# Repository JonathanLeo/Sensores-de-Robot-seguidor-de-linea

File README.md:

# Sensores-de-Robot-seguidor-de-linea
Esquemático y Board

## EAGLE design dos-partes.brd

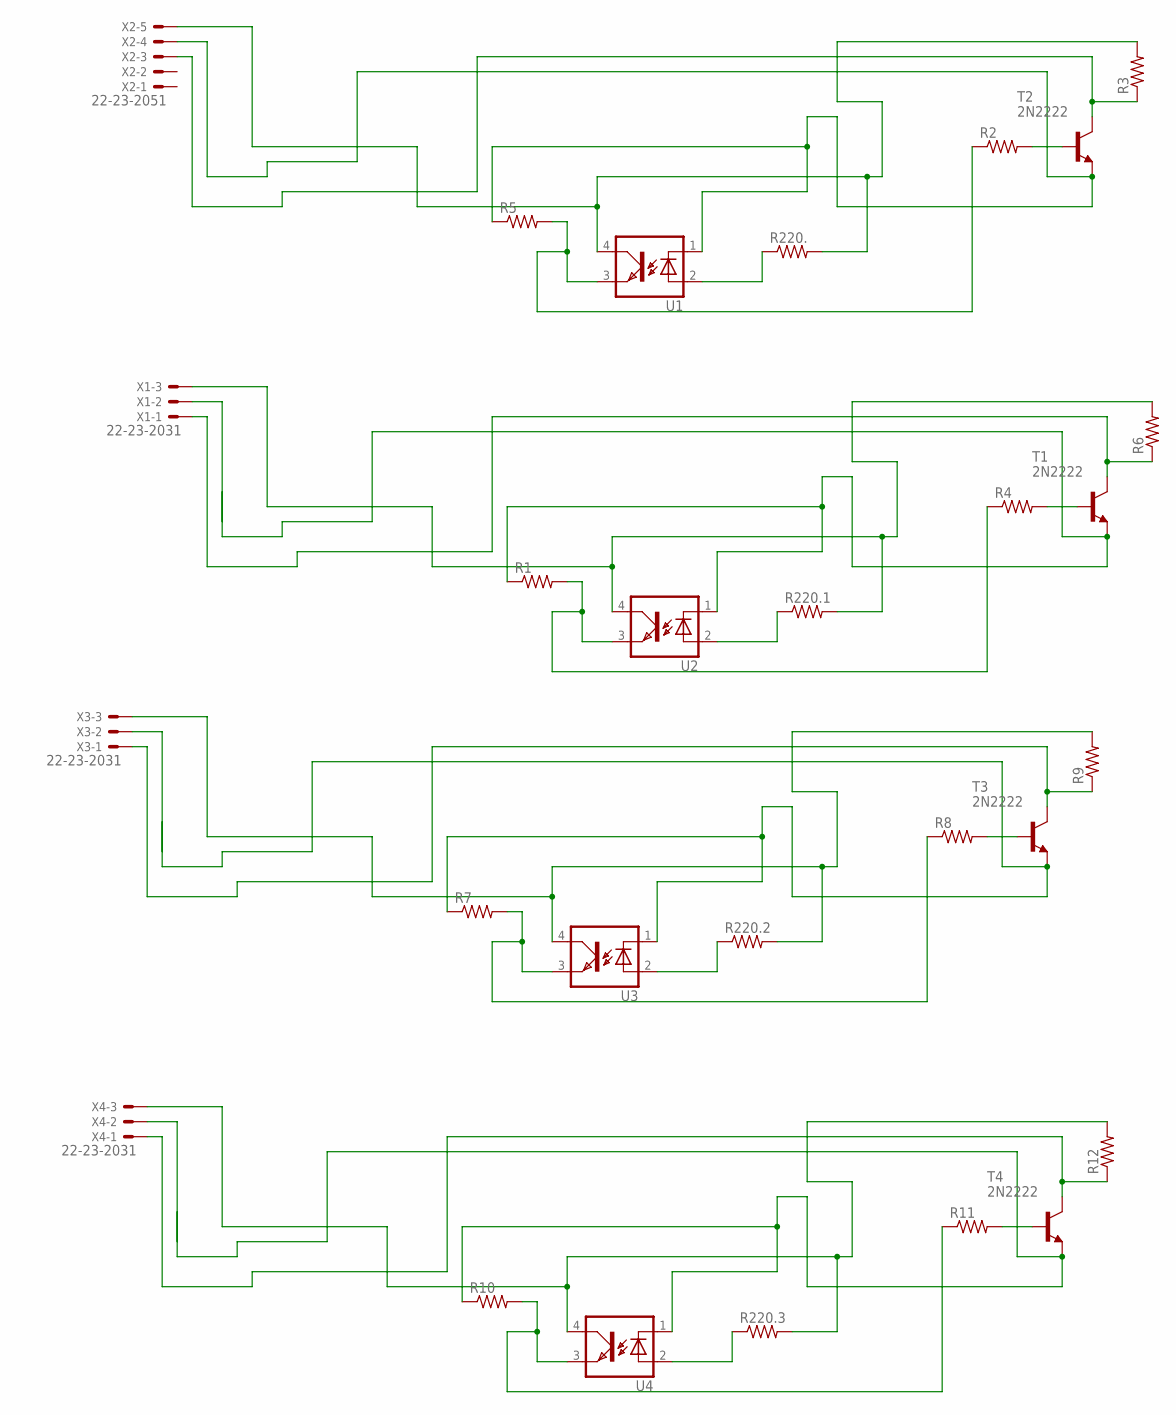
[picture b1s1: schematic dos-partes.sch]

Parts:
R1, R2, R3, R4, R5, R6, R7, R8, R9, R10, R11, R12, R220., R220.1, R220.2, R220.3: R-US_0204/7; 0204/7
T1, T2, T3, T4: 2N2222; TO18
U1, U2, U3, U4: CNY70
X1, X3, X4: 22-23-2031
X2: 22-23-2051

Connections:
unnamed: R220..1, U1.2
unnamed: R5.1, T2.1 (E), U1.1, X2.4
unnamed: R2.1, R5.2, U1.3
unnamed: R2.2, T2.2 (B)
unnamed: R220.1.1, U2.2
unnamed: R3.1, T2.3 (C), X2.3
unnamed: R1.2, R4.1, U2.3
unnamed: R4.2, T1.2 (B)
unnamed: R1.1, T1.1 (E), U2.1, X1.2
unnamed: R3.2, R220..2, U1.4, X2.5
unnamed: R6.2, R220.1.2, U2.4, X1.3
unnamed: R220.2.1, U3.2
unnamed: R7.2, R8.1, U3.3
unnamed: R8.2, T3.2 (B)
unnamed: R7.1, T3.1 (E), U3.1, X3.2
unnamed: R9.2, R220.2.2, U3.4, X3.3
unnamed: R9.1, T3.3 (C), X3.1
unnamed: R220.3.1, U4.2
unnamed: R10.2, R11.1, U4.3
unnamed: R11.2, T4.2 (B)
unnamed: R10.1, T4.1 (E), U4.1, X4.2
unnamed: R12.2, R220.3.2, U4.4, X4.3
unnamed: R12.1, T4.3 (C), X4.1
unnamed: R6.1, T1.3 (C), X1.1

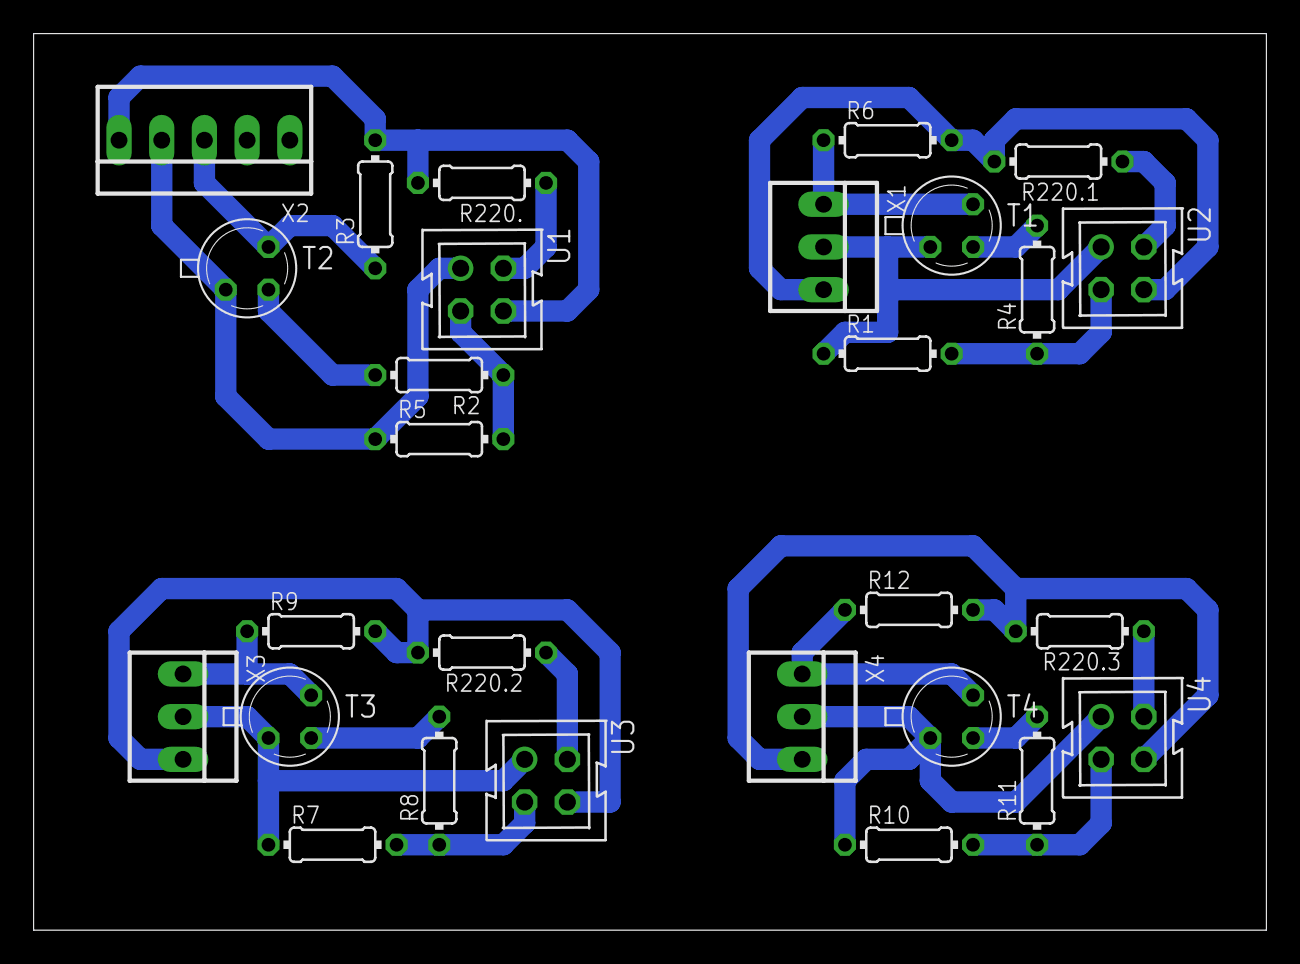
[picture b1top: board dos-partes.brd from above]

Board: 2 copper layers, 73.3 x 53.3 mm, 28 parts (0 on the bottom side), 24 nets.

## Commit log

2018-06-01 Sensores de Robot seguidor de linea
